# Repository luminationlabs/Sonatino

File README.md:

# Sonatino "Bluetooth Audio Edition" PCB Design Files

This is an unreleased variant of the [Sonatino](https://github.com/luminationlabs/Sonatino) board that adds support for Bluetooth audio by using the ESP32 microcontroller in place of ESP32-S3.

## Features

- ESP32-WROOM-32UE MCU with 16MB flash
- High-quality 24-bit/192kHz DAC (WM8524, stereo) and ADC (WM8782, mono)
- 3.2W speaker amplifier (MAX98357A)
- TRRS audio jack supporting input and output
- Stereo headphone amplifier and microphone preamp
- microSD card slot
- WiFi and Bluetooth v4.2 BR/EDR and BLE
- Bluetooth audio (A2DP) support
- USB-C for programming and power
- Battery support with charging circuit
- Configurable audio I/O levels
- Compact form factor

## Component Availability

The ADC that Sonatino uses (Cirrus Logic WM8782) has been discontinued by its manufacturer. Some suppliers may still have limited stock, but ultimately it needs to be replaced with a similar ADC (possibly a Texas Instruments PCM186x chip or an audio CODEC to replace the ADC and DAC). In either case, the PCB schematic and layout will need to be modified as there is no drop-in replacement.

## Board Variants

### [Sonatino](https://github.com/luminationlabs/Sonatino) (`main` branch)

- Standard board documented at [sonatino.com](https://sonatino.com)
- Based on ESP32-S3-WROOM-1U
- Uses Bluetooth 5.0 LE **without** support for Bluetooth audio

### [Sonatino - Bluetooth Audio Edition](https://github.com/luminationlabs/Sonatino/tree/btaudio) (`btaudio` branch)

- Unreleased board
- Based on ESP32-WROOM-32UE
- Uses Bluetooth v4.2 BR/EDR **with** support for Bluetooth audio (A2DP)
- Has fewer exposed GPIO pins (10 vs 13)
- Requires configuration using shift register on GPIO 17, 18, and 19

## License and Trademark Notice

Certified open source hardware ([oshwa.org/cert](https://oshwa.org/cert)) - [OSHW] US002724

The design files for this PCB are open-source hardware under [CERN OHL-P v2.0](https://ohwr.org/cern_ohl_p_v2.txt).

The name "Sonatino" and the associated logo are trademarks of Lumination Labs, Inc. Other manufacturers may use the hardware design but may not use the "Sonatino" branding without permission.

The documentation for Sonatino is copyrighted by Lumination Labs, Inc. and provided for informational purposes only. Redistribution or modification of the documentation requires written permission.

## Documentation

Documentation and examples for the standard Sonatino board (not this variant) can be found here:

- [Documentation](https://sonatino.com/docs/)
- [Example Projects](https://github.com/luminationlabs/Sonatino-Examples)

Pin configurations will need to be modified for use with the "Bluetooth Audio Edition" according to those found in the schematic. Audio configuration requires the use of a shift register on GPIO 17, 18, and 19 (SER, SRCLK, and RCLK).

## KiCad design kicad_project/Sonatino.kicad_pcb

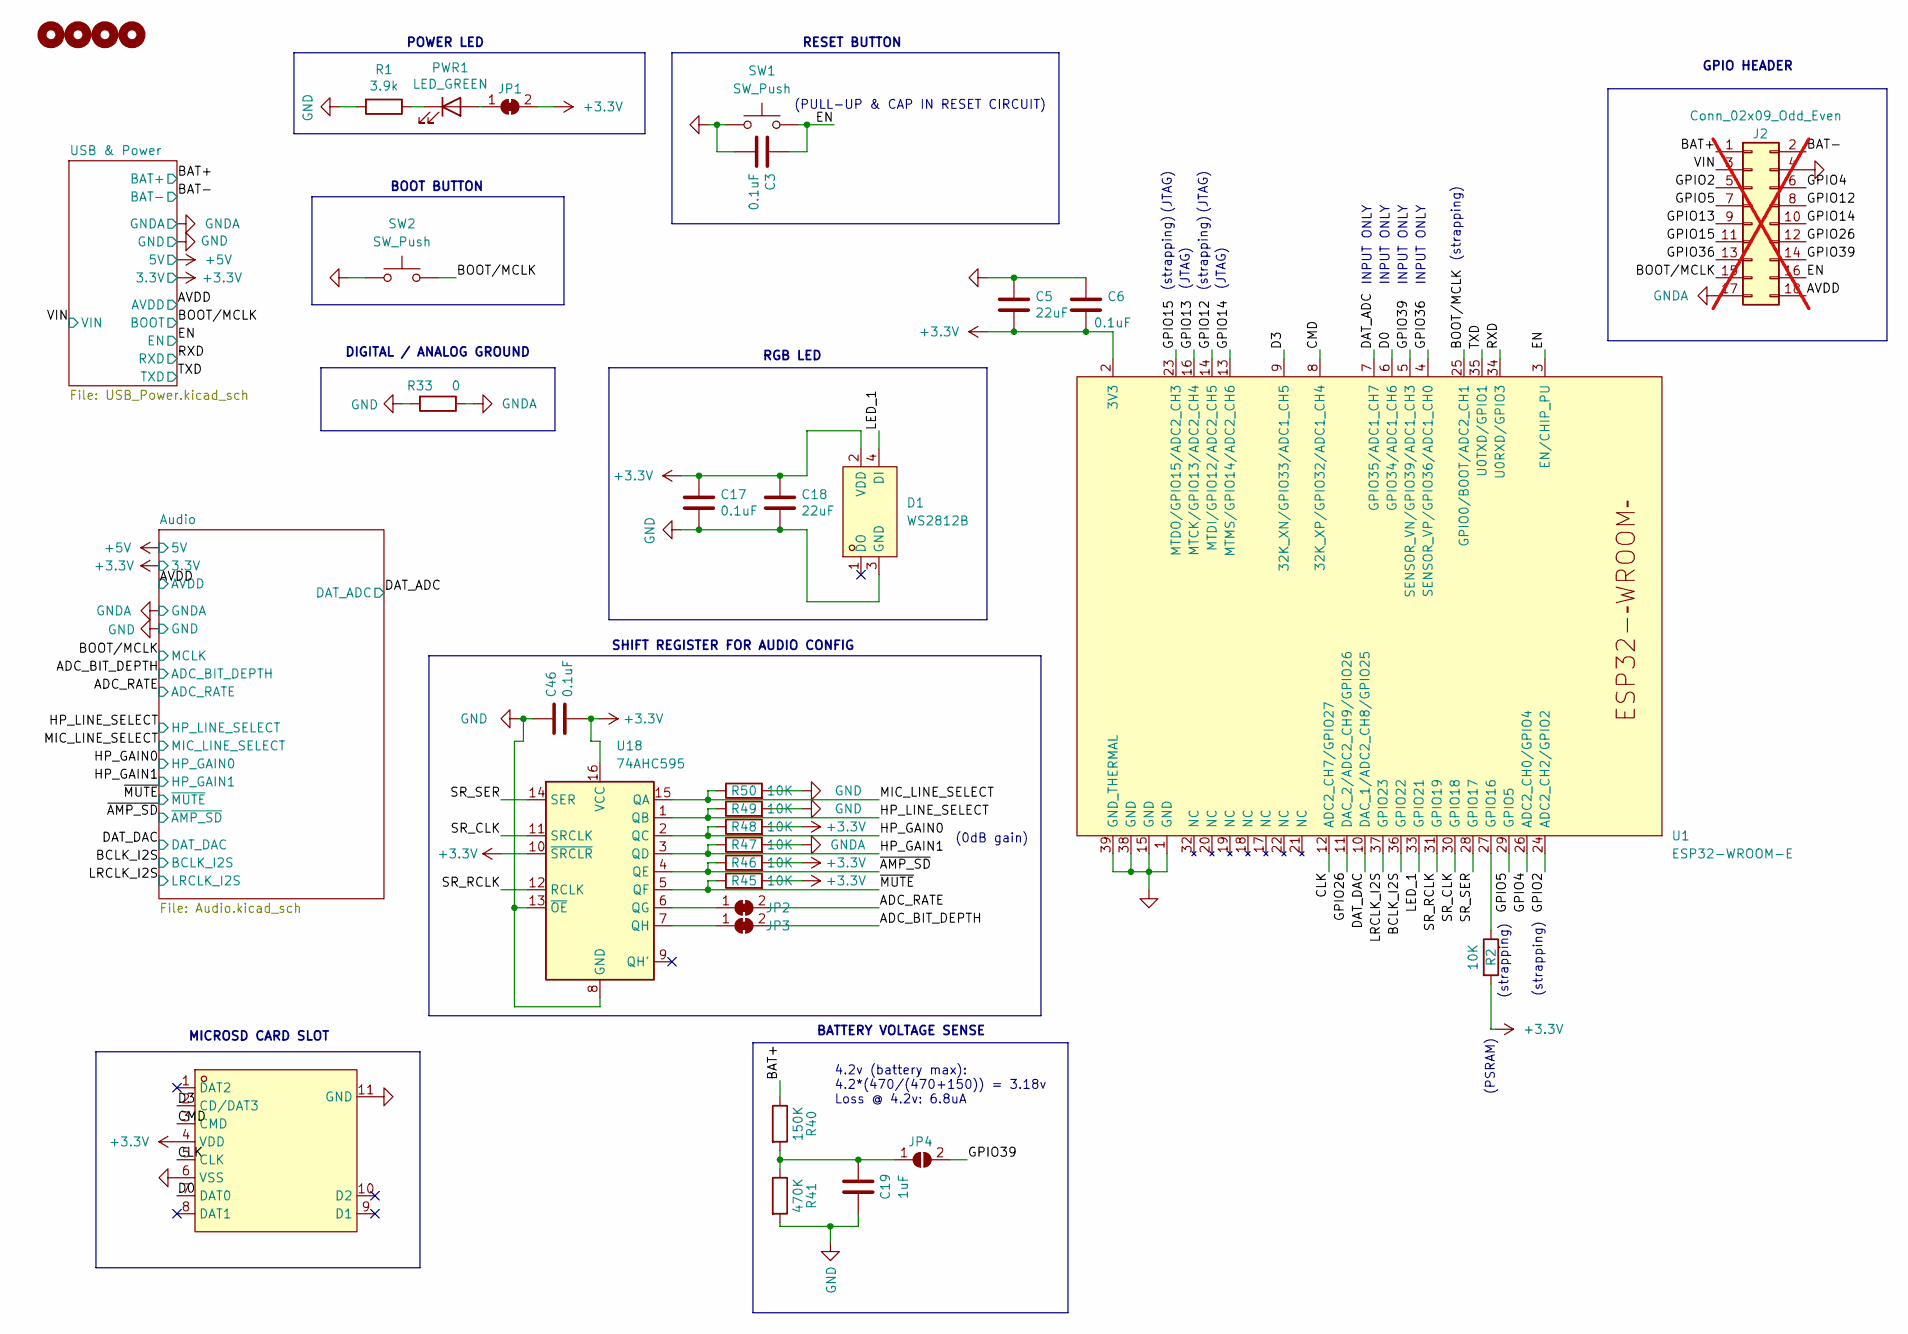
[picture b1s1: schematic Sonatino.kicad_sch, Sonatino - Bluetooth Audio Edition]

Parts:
C3, C6, C17, C46: 0.1uF; C_0402_1005Metric; LCSC C307331
C5: 22uF; C_0805_2012Metric; LCSC C45783
C18: 22uF; C_0603_1608Metric; LCSC C59461
C19: 1uF; C_0402_1005Metric; LCSC C52923
Card1: TF-008; TF-SMD_TF-008; LCSC Part C428465
D1: WS2812B; LED-SMD_4P-L1.6-W1.5_XL-1615RGBC-WS2812B; LCSC C5349954
H1, H3, H5, H7: MountingHole; MountingHole_2.7mm_Pad; LCSC 0
J2: Conn_02x09_Odd_Even; PinHeader_2x09_P2.54mm_Vertical; LCSC 0; not fitted
JP1, JP2, JP3: SolderJumper_2_Bridged; SolderJumper-2_P1.3mm_Bridged_Pad1.0x1.5mm; LCSC 0
JP4: SolderJumper_2_Open; SolderJumper-2_P1.3mm_Open_TrianglePad1.0x1.5mm
PWR1: LED_GREEN; LED_0603_1608Metric; LCSC C12624
R1: 3.9k; R_0402_1005Metric; LCSC C51721
R2, R45, R46, R47, R48, R49, R50: 10K; R_0402_1005Metric; LCSC C25744
R33: 0; R_0603_1608Metric; LCSC C21189
R40: 150K; R_0402_1005Metric; LCSC C102813
R41: 470K; R_0402_1005Metric; LCSC C25790
SW1, SW2: SW_Push; SW_Push_1P1T_NO_3.95_2.9; LCSC C354946
U1: ESP32-WROOM-E; ESP32-WROOM-32UE; LCSC C701346
U18: 74AHC595; X1-QFN-16-EP_L2.5-W2.5-P0.40-BL-EP1.4; LCSC C2682068

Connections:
+3.3V: C5.2, C6.2, C17.1, C18.1, C46.2, Card1.4 (VDD), D1.2 (VDD), JP1.2 (B), R2.2, R45.2, R46.2, R48.2, U1.2 (3V3), U18.10 (~SRCLR), U18.16 (VCC); also elsewhere on the board
/ADC_BIT_DEPTH: JP3.2 (B); also elsewhere on the board
/ADC_RATE: JP2.2 (B); also elsewhere on the board
/AVDD: J2.18; also elsewhere on the board
/BAT+: J2.1, R40.1; also elsewhere on the board
/BAT-: J2.2; also elsewhere on the board
/BCLK_I2S: U1.36 (GPIO22); also elsewhere on the board
/BOOT/MCLK: J2.15, SW2.2, U1.25 (GPIO0/BOOT/ADC2_CH1); also elsewhere on the board
/CLK: Card1.5 (CLK), U1.12 (ADC2_CH7/GPIO27)
/CMD: Card1.3 (CMD), U1.8 (32K_XP/GPIO32/ADC1_CH4)
/D0: Card1.7 (DAT0), U1.6 (GPIO34/ADC1_CH6)
/D3: Card1.2 (CD/DAT3), U1.9 (32K_XN/GPIO33/ADC1_CH5)
/DAT_ADC: U1.7 (GPIO35/ADC1_CH7); also elsewhere on the board
/DAT_DAC: U1.10 (DAC_1/ADC2_CH8/GPIO25); also elsewhere on the board
/EN: C3.1, J2.16, SW1.2, U1.3 (EN/CHIP_PU); also elsewhere on the board
/GPIO2: J2.5, U1.24 (ADC2_CH2/GPIO2)
/GPIO4: J2.6, U1.26 (ADC2_CH0/GPIO4)
/GPIO5: J2.7, U1.29 (GPIO5)
/GPIO12: J2.8, U1.14 (MTDI/GPIO12/ADC2_CH5)
/GPIO13: J2.9, U1.16 (MTCK/GPIO13/ADC2_CH4)
/GPIO14: J2.10, U1.13 (MTMS/GPIO14/ADC2_CH6)
/GPIO15: J2.11, U1.23 (MTDO/GPIO15/ADC2_CH3)
/GPIO26: J2.12, U1.11 (DAC_2/ADC2_CH9/GPIO26)
/GPIO36: J2.13, U1.4 (SENSOR_VP/GPIO36/ADC1_CH0)
/GPIO39: J2.14, JP4.2 (B), U1.5 (SENSOR_VN/GPIO39/ADC1_CH3)
/HP_GAIN0: R48.1, U18.2 (QC); also elsewhere on the board
/HP_GAIN1: R47.1, U18.3 (QD); also elsewhere on the board
/HP_LINE_SELECT: R49.1, U18.1 (QB); also elsewhere on the board
/LED_1: D1.4 (DI), U1.33 (GPIO21)
/LRCLK_I2S: U1.37 (GPIO23); also elsewhere on the board
/MIC_LINE_SELECT: R50.1, U18.15 (QA); also elsewhere on the board
/RXD: U1.34 (U0RXD/GPIO3); also elsewhere on the board
/SR_CLK: U1.30 (GPIO18), U18.11 (SRCLK)
/SR_RCLK: U1.31 (GPIO19), U18.12 (RCLK)
/SR_SER: U1.28 (GPIO17), U18.14 (SER)
/TXD: U1.35 (U0TXD/GPIO1); also elsewhere on the board
/VIN: J2.3; also elsewhere on the board
/~AMP_SD: R46.1, U18.4 (QE); also elsewhere on the board
/~MUTE: R45.1, U18.5 (QF); also elsewhere on the board
GND: C3.2, C5.1, C6.1, C17.2, C18.2, C19.1, C46.1, Card1.6 (VSS), Card1.11 (GND), D1.3 (GND), J2.4, R1.2, R33.2, R41.2, R49.2, R50.2, SW1.1, SW2.1, U1.1 (GND), U1.15 (GND), U1.38 (GND), U1.39 (GND_THERMAL), U18.8 (GND), U18.13 (~OE); also elsewhere on the board
GNDA: J2.17, R33.1, R47.2; also elsewhere on the board
unnamed: JP1.1 (A), PWR1.2 (A)
unnamed: JP2.1 (A), U18.6 (QG)
unnamed: JP3.1 (A), U18.7 (QH)
unnamed: C19.2, JP4.1 (A), R40.2, R41.1
unnamed: PWR1.1 (K), R1.1
unnamed: R2.1, U1.27 (GPIO16)

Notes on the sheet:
(PSRAM)
(JTAG)
GPIO HEADER
(strapping)
POWER LED
MICROSD CARD SLOT
INPUT ONLY
RESET BUTTON
BOOT BUTTON
BATTERY VOLTAGE SENSE
(0dB gain)
(PULL-UP & CAP IN RESET CIRCUIT)
DIGITAL / ANALOG GROUND
RGB LED
4.2v (battery max): 4.2*(470/(470+150)) = 3.18v Loss @ 4.2v: 6.8uA
SHIFT REGISTER FOR AUDIO CONFIG

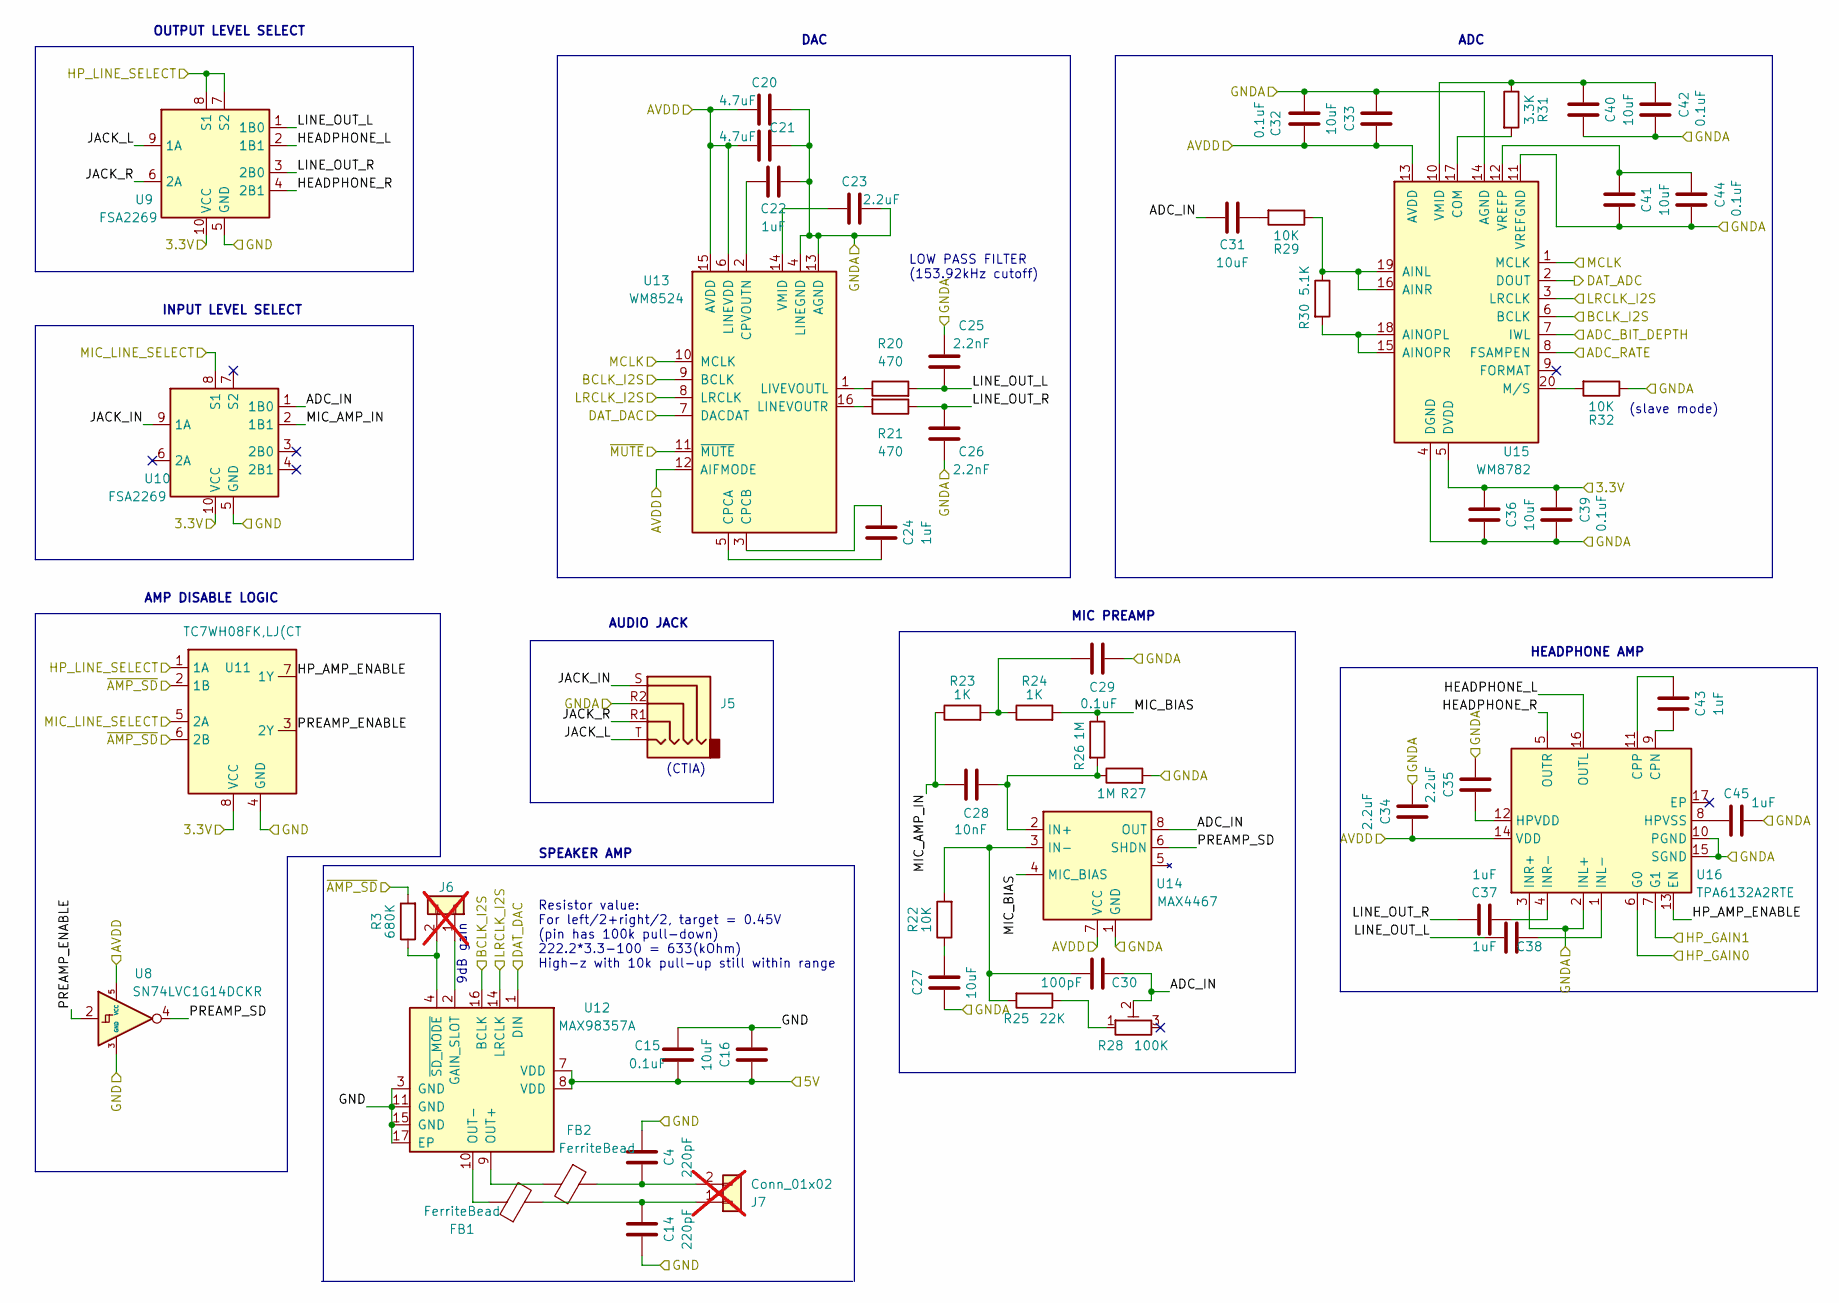
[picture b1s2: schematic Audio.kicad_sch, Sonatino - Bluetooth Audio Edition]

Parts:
C4, C14: 220pF; C_0402_1005Metric; LCSC C1530
C15: 0.1uF; C_0805_2012Metric; LCSC C49678
C16: 10uF; C_0805_2012Metric; LCSC C15850
C20, C21: 4.7uF; C_0402_1005Metric; LCSC C23733
C22, C37, C38, C43, C45: 1uF; C_0402_1005Metric; LCSC C52923
C23, C34, C35: 2.2uF; C_0402_1005Metric; LCSC C12530
C24: 1uF; C_0603_1608Metric; LCSC C15849
C25, C26: 2.2nF; C_0402_1005Metric; LCSC C1531
C27, C31, C33, C36, C40, C41: 10uF; C_0402_1005Metric; LCSC C15525
C28: 10nF; C_0402_1005Metric; LCSC C15195
C29, C32, C39, C42, C44: 0.1uF; C_0402_1005Metric; LCSC C307331
C30: 100pF; C_0402_1005Metric; LCSC C1546
FB1, FB2: FerriteBead; L_0603_1608Metric; LCSC C1002
J5: AudioJack4; PJ-321B; LCSC C692436
J6: Conn_01x02; PinHeader_1x02_P2.54mm_Vertical; not fitted
J7: Conn_01x02; PinHeader_1x02_P2.54mm_Vertical; LCSC 0; not fitted
R3: 680K; R_0603_1608Metric; LCSC C25822
R20, R21: 470; R_0402_1005Metric; LCSC C25117
R22, R29, R32: 10K; R_0402_1005Metric; LCSC C25744
R23, R24: 1K; R_0402_1005Metric; LCSC C11702
R25: 22K; R_0402_1005Metric; LCSC C25768
R26, R27: 1M; R_0402_1005Metric; LCSC C26083
R28: 100K; G32AT-B103; LCSC C128123
R30: 5.1K; R_0402_1005Metric; LCSC C25905
R31: 3.3K; R_0402_1005Metric; LCSC C25890
U8: SN74LVC1G14DCKR; SOT-353_SC-70-5; LCSC C2976657
U9, U10: FSA2269; Fairchild_MicroPak-10_2.10x1.6mm_P0.5mm; LCSC C895405
U11: TC7WH08FK,LJ(CT; VSSOP-8_2.3x2mm_P0.5mm; LCSC C2880449
U12: MAX98357A; TQFN-16-1EP_3x3mm_P0.5mm_EP1.23x1.23mm; JLCPCB Rotation Offset 270
U13: WM8524; TSSOP-16_4.4x5mm_P0.65mm; LCSC C146242
U14: MAX4467; SOT-23-8; LCSC C490742
U15: WM8782; SSOP-20_5.3x7.2mm_P0.65mm; LCSC C323842
U16: TPA6132A2RTE; WQFN-16-1EP_3x3mm_P0.5mm_EP1.6x1.6mm_ThermalVias; LCSC C69901

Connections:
+3.3V: C36.2, C39.1, U9.10 (VCC), U10.10 (VCC), U11.8 (VCC), U15.5 (DVDD); also elsewhere on the board
+5V: C15.1, C16.2, U12.7 (VDD), U12.8 (VDD); also elsewhere on the board
/ADC_BIT_DEPTH: U15.7 (IWL); also elsewhere on the board
/ADC_RATE: U15.8 (FSAMPEN); also elsewhere on the board
/AVDD: C20.1, C21.1, C32.1, C33.2, C34.2, U8.5 (VCC), U13.6 (LINEVDD), U13.12 (AIFMODE), U13.15 (AVDD), U14.7 (VCC), U15.13 (AVDD), U16.14 (VDD); also elsewhere on the board
/Audio/ADC_IN: C30.2, C31.1, R28.2, U10.1 (1B0), U14.8 (OUT)
/Audio/HEADPHONE_L: U9.2 (1B1), U16.16 (OUTL)
/Audio/HEADPHONE_R: U9.4 (2B1), U16.5 (OUTR)
/Audio/HP_AMP_ENABLE: U11.7 (1Y), U16.13 (EN)
/Audio/JACK_IN: J5.S, U10.9 (1A)
/Audio/JACK_L: J5.T, U9.9 (1A)
/Audio/JACK_R: J5.R1, U9.6 (2A)
/Audio/LINE_OUT_L: C25.1, C38.1, R20.2, U9.1 (1B0)
/Audio/LINE_OUT_R: C26.2, C37.2, R21.1, U9.3 (2B0)
/Audio/MIC_AMP_IN: C28.2, R23.1, U10.2 (1B1)
/Audio/MIC_BIAS: R24.2, R26.1, U14.4 (MIC_BIAS)
/Audio/PREAMP_ENABLE: U8.2, U11.3 (2Y)
/Audio/PREAMP_SD: U8.4, U14.6 (SHDN)
/BCLK_I2S: U12.16 (BCLK), U13.9 (BCLK), U15.6 (BCLK); also elsewhere on the board
/BOOT/MCLK: U13.10 (MCLK), U15.1 (MCLK); also elsewhere on the board
/DAT_ADC: U15.2 (DOUT); also elsewhere on the board
/DAT_DAC: U12.1 (DIN), U13.7 (DACDAT); also elsewhere on the board
/HP_GAIN0: U16.6 (G0); also elsewhere on the board
/HP_GAIN1: U16.7 (G1); also elsewhere on the board
/HP_LINE_SELECT: U9.7 (S2), U9.8 (S1), U11.1 (1A); also elsewhere on the board
/LRCLK_I2S: U12.14 (LRCLK), U13.8 (LRCLK), U15.3 (LRCLK); also elsewhere on the board
/MIC_LINE_SELECT: U10.8 (S1), U11.5 (2A); also elsewhere on the board
/~AMP_SD: R3.2, U11.2 (1B), U11.6 (2B); also elsewhere on the board
/~MUTE: U13.11 (~MUTE); also elsewhere on the board
GND: C4.2, C14.1, C15.2, C16.1, U8.3 (GND), U9.5 (GND), U10.5 (GND), U11.4 (GND), U12.3 (GND), U12.11 (GND), U12.15 (GND), U12.17 (EP); also elsewhere on the board
GNDA: C20.2, C21.2, C22.2, C23.1, C25.2, C26.1, C27.2, C29.1, C32.2, C33.1, C34.1, C35.1, C36.1, C39.2, C40.1, C41.1, C42.2, C44.2, C45.1, J5.R2, R27.2, R32.1, U13.4 (LINEGND), U13.13 (AGND), U14.1 (GND), U15.4 (DGND), U15.11 (VREFGND), U15.14 (AGND), U16.2 (INL+), U16.3 (INR+), U16.10 (PGND), U16.15 (SGND); also elsewhere on the board
unnamed: C27.1, R22.1
unnamed: C29.2, R23.2, R24.1
unnamed: C31.2, R29.2
unnamed: J6.1, U12.2 (GAIN_SLOT)
unnamed: J6.2, R3.1, U12.4 (~SD_MODE)
unnamed: C14.2, FB1.2, J7.1
unnamed: C4.1, FB2.1, J7.2
unnamed: R25.1, R28.1
unnamed: FB2.2, U12.9 (OUT+)
unnamed: FB1.1, U12.10 (OUT-)
unnamed: C24.1, U13.5 (CPCA)
unnamed: C24.2, U13.3 (CPCB)
unnamed: C22.1, U13.2 (CPVOUTN)
unnamed: R21.2, U13.16 (LINEVOUTR)
unnamed: R20.1, U13.1 (LIVEVOUTL)
unnamed: C23.2, U13.14 (VMID)
unnamed: C28.1, R26.2, R27.1, U14.2 (IN+)
unnamed: C30.1, R22.2, R25.2, U14.3 (IN-)
unnamed: R29.1, R30.1, U15.16 (AINR), U15.19 (AINL)
unnamed: R30.2, U15.15 (AINOPR), U15.18 (AINOPL)
unnamed: R31.2, U15.17 (COM)
unnamed: R32.2, U15.20 (M/S)
unnamed: C40.2, C42.1, R31.1, U15.10 (VMID)
unnamed: C41.2, C44.1, U15.12 (VREFP)
unnamed: C43.1, U16.9 (CPN)
unnamed: C43.2, U16.11 (CPP)
unnamed: C35.2, U16.12 (HPVDD)
unnamed: C45.2, U16.8 (HPVSS)
unnamed: C38.2, U16.1 (INL-)
unnamed: C37.1, U16.4 (INR-)

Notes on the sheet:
ADC
MIC PREAMP
LOW PASS FILTER (153.92kHz cutoff)
Resistor value: For left/2+right/2, target = 0.45V (pin has 100k pull-down) 222.2*3.3-100 = 633(kOhm) High-z with 10k pull-up still within range
INPUT LEVEL SELECT
(slave mode)
AMP DISABLE LOGIC
AUDIO JACK
OUTPUT LEVEL SELECT
DAC
SPEAKER AMP
HEADPHONE AMP
(CTIA)
9dB gain

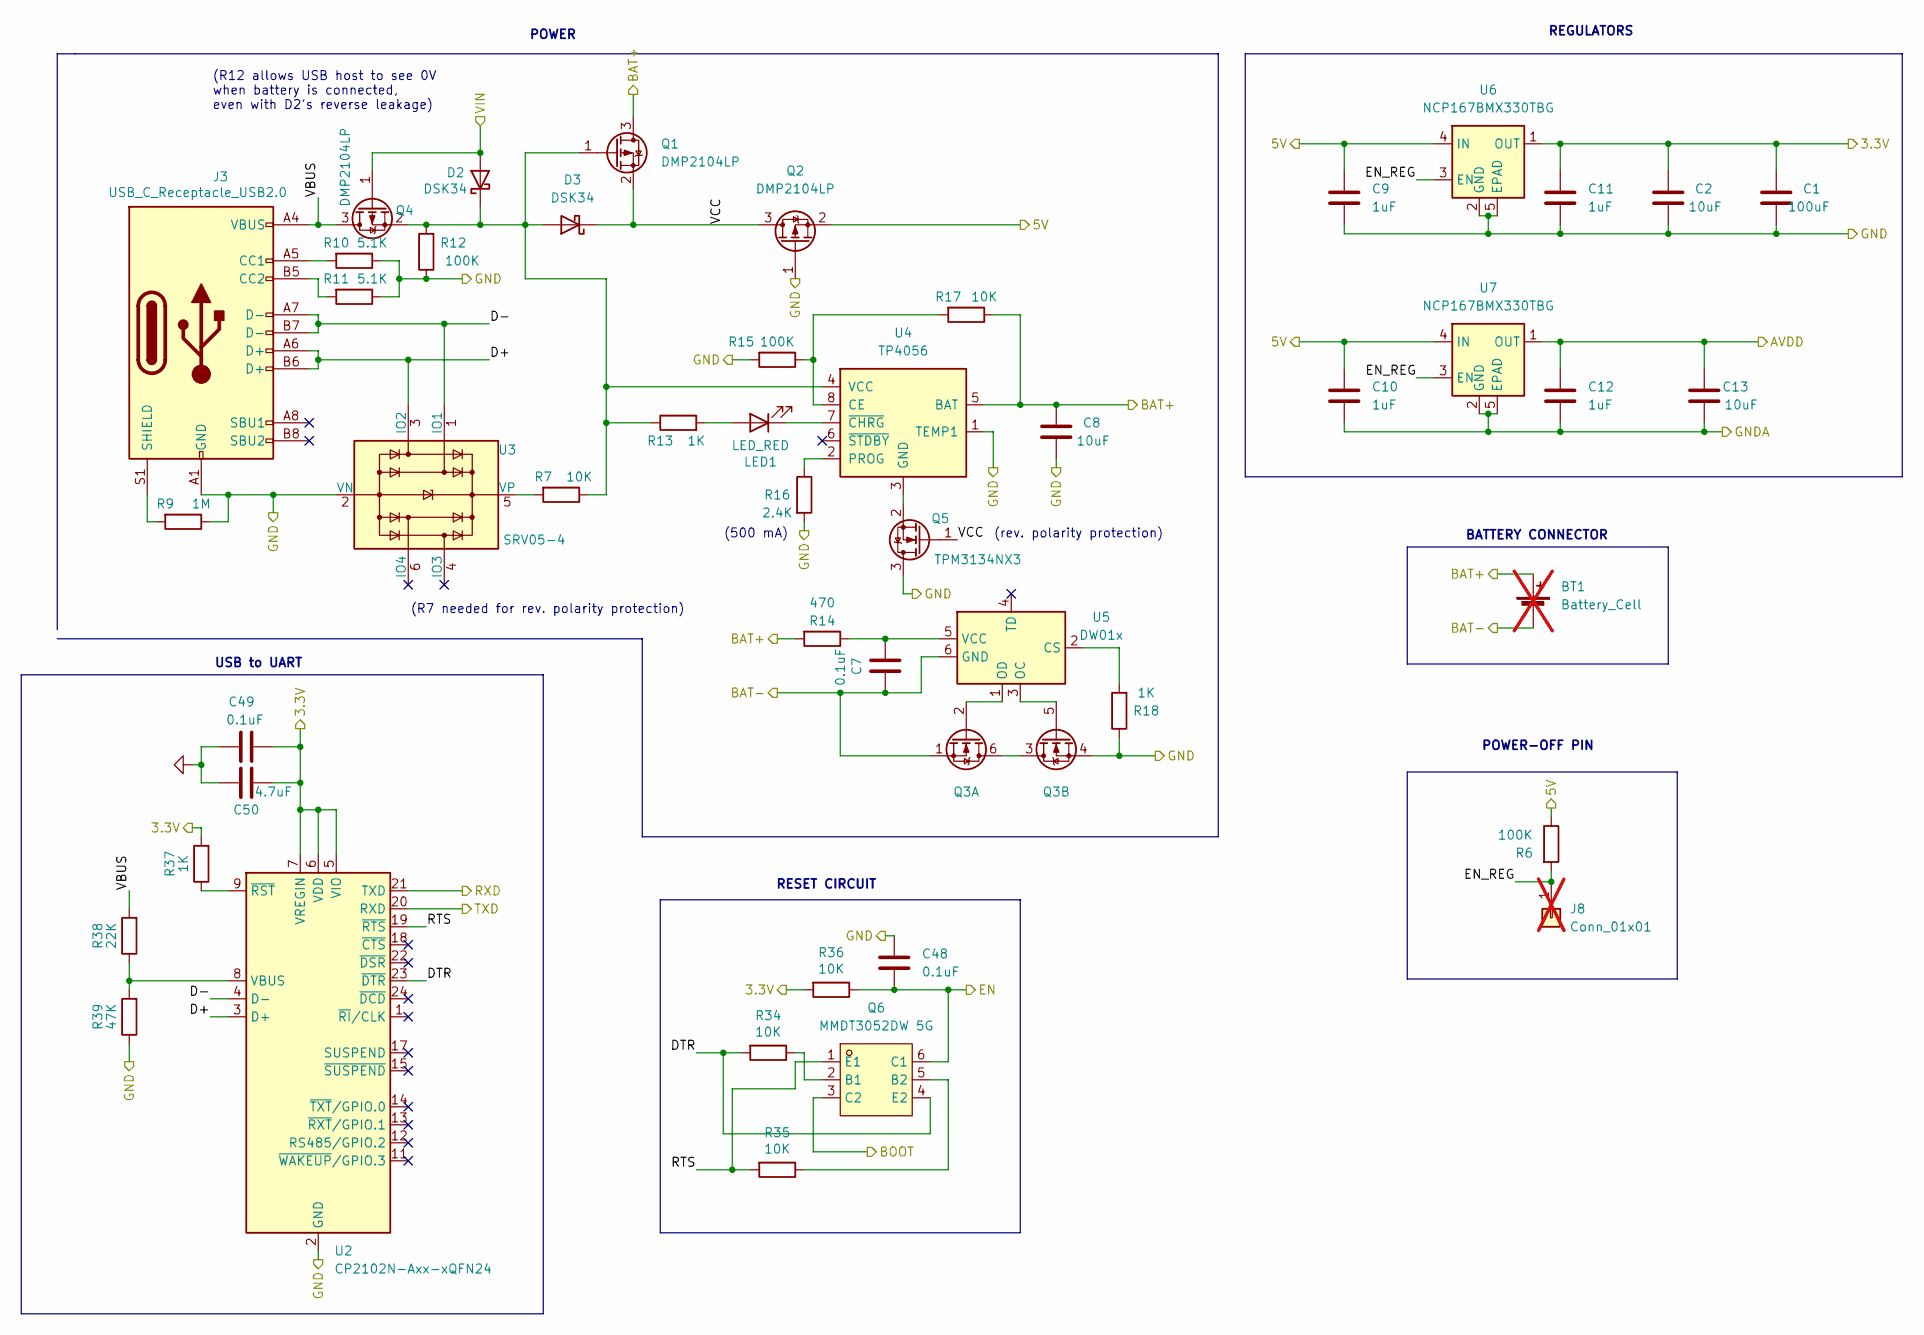
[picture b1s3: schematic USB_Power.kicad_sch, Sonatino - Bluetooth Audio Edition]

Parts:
BT1: Battery_Cell; JST_PH_S2B-PH-SM4-TB_1x02-1MP_P2.00mm_Horizontal; LCSC 0; not fitted
C1: 100uF; C_1206_3216Metric; LCSC C15008
C2, C13: 10uF; C_0603_1608Metric; LCSC C19702
C7, C48, C49: 0.1uF; C_0402_1005Metric; LCSC C307331
C8: 10uF; C_0402_1005Metric; LCSC C15525
C9, C10, C11, C12: 1uF; C_0402_1005Metric; LCSC C52923
C50: 4.7uF; C_0402_1005Metric; LCSC C23733
D2, D3: DSK34; SOD-123FL; LCSC C41029
J3: USB_C_Receptacle_USB2.0; USB_C_Receptacle_HRO_TYPE-C-31-M-12; LCSC C165948
J8: Conn_01x01; PinHeader_1x01_P2.54mm_Vertical; LCSC 0; not fitted
LED1: LED_RED; LED_0603_1608Metric; LCSC C2286
Q1, Q2, Q4: DMP2104LP; Diodes_DFN1411-3; LCSC C260933
Q3: HSCC8233; DFN-6-1EP_3x2mm_P0.5mm_EP1.65x1.35mm_Dual_MOSFETs; LCSC C700968
Q5: TPM3134NX3; SOT-723; LCSC C558450
Q6: MMDT3052DW 5G; SOT-363_SC-70-6; LCSC C2928254
R6, R12, R15: 100K; R_0402_1005Metric; LCSC C25741
R7, R17, R34, R35, R36: 10K; R_0402_1005Metric; LCSC C25744
R9: 1M; R_0402_1005Metric; LCSC C26083
R10, R11: 5.1K; R_0402_1005Metric; LCSC C25905
R13, R18, R37: 1K; R_0402_1005Metric; LCSC C11702
R14: 470; R_0402_1005Metric; LCSC C25117
R16: 2.4K; R_0402_1005Metric; LCSC C25882
R38: 22K; R_0402_1005Metric; LCSC C25768
R39: 47K; R_0402_1005Metric; LCSC C25792
U2: CP2102N-Axx-xQFN24; QFN-24-1EP_4x4mm_P0.5mm_EP2.6x2.6mm; LCSC C969151
U3: SRV05-4; SOT-23-6; LCSC C85364
U4: TP4056; TI_SO-PowerPAD-8; LCSC C16581
U5: DW01x; SOT-23-6; LCSC C351410
U6, U7: NCP167BMX330TBG; OnSemi_XDFN4-1EP_1.0x1.0mm_EP0.52x0.52mm-FIXED; LCSC C892227

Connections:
+3.3V: C1.2, C2.2, C11.1, C49.2, C50.1, R36.2, R37.2, U2.5 (VIO), U2.6 (VDD), U2.7 (VREGIN), U6.1 (OUT); also elsewhere on the board
+5V: C9.1, C10.1, Q2.2 (S), R6.1, U6.4 (IN), U7.4 (IN); also elsewhere on the board
/AVDD: C12.1, C13.2, U7.1 (OUT); also elsewhere on the board
/BAT+: BT1.1 (+), C8.2, Q1.3 (D), R14.2, R17.1, U4.5 (BAT); also elsewhere on the board
/BAT-: BT1.2 (-), C7.1, Q3.1 (S), U5.6 (GND); also elsewhere on the board
/BOOT/MCLK: Q6.3 (C2); also elsewhere on the board
/EN: C48.2, Q6.6 (C1), R36.1; also elsewhere on the board
/RXD: U2.21 (TXD); also elsewhere on the board
/TXD: U2.20 (RXD); also elsewhere on the board
/USB & Power/D+: J3.A6 (D+), J3.B6 (D+), U2.3 (D+), U3.3 (IO2)
/USB & Power/D-: J3.A7 (D-), J3.B7 (D-), U2.4 (D-), U3.1 (IO1)
/USB & Power/DTR: Q6.4 (E2), R34.2, U2.23 (~DTR)
/USB & Power/EN_REG: J8.1, R6.2, U6.3 (EN), U7.3 (EN)
/USB & Power/RTS: Q6.1 (E1), R35.2, U2.19 (~RTS)
/USB & Power/VBUS: J3.A4 (VBUS), J3.A9 (VBUS), J3.B4 (VBUS), J3.B9 (VBUS), Q4.3 (D), R38.2
/USB & Power/VCC: D3.1 (K), Q1.2 (S), Q2.3 (D), Q5.1 (G)
/VIN: D2.2 (A), Q4.1 (G); also elsewhere on the board
GND: C1.1, C2.1, C8.1, C9.2, C11.2, C48.1, C49.1, C50.2, J3.A1 (GND), J3.A12 (GND), J3.B1 (GND), J3.B12 (GND), Q2.1 (G), Q3.4 (S), Q5.3 (D), R9.1, R10.1, R11.1, R12.1, R15.2, R16.2, R18.1, R39.1, U2.2 (GND), U2.25 (GND), U3.2 (VN), U4.1 (TEMP1), U6.2 (GND), U6.5 (EPAD); also elsewhere on the board
GNDA: C10.2, C12.2, C13.1, U7.2 (GND), U7.5 (EPAD); also elsewhere on the board
unnamed: D2.1 (K), D3.2 (A), Q1.1 (G), Q4.2 (S), R7.1, R12.2, R13.1, U4.4 (VCC)
unnamed: J3.A5 (CC1), R10.2
unnamed: J3.B5 (CC2), R11.2
unnamed: J3.S1 (SHIELD), R9.2
unnamed: LED1.2 (A), R13.2
unnamed: LED1.1 (K), U4.7 (~CHRG)
unnamed: Q3.3 (D), Q3.6 (D)
unnamed: Q3.2 (G), U5.1 (OD)
unnamed: Q3.5 (G), U5.3 (OC)
unnamed: Q5.2 (S), U4.3 (GND)
unnamed: Q6.2 (B1), R34.1
unnamed: Q6.5 (B2), R35.1
unnamed: R38.1, R39.2, U2.8 (VBUS)
unnamed: R37.1, U2.9 (~RST)
unnamed: R7.2, U3.5 (VP)
unnamed: R15.1, R17.2, U4.8 (CE)
unnamed: R16.1, U4.2 (PROG)
unnamed: R18.2, U5.2 (CS)
unnamed: C7.2, R14.1, U5.5 (VCC)

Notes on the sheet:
(rev. polarity protection)
RESET CIRCUIT
POWER-OFF PIN
(500 mA)
USB to UART
POWER
REGULATORS
(R7 needed for rev. polarity protection)
BATTERY CONNECTOR
(R12 allows USB host to see 0V when battery is connected, even with D2's reverse leakage)

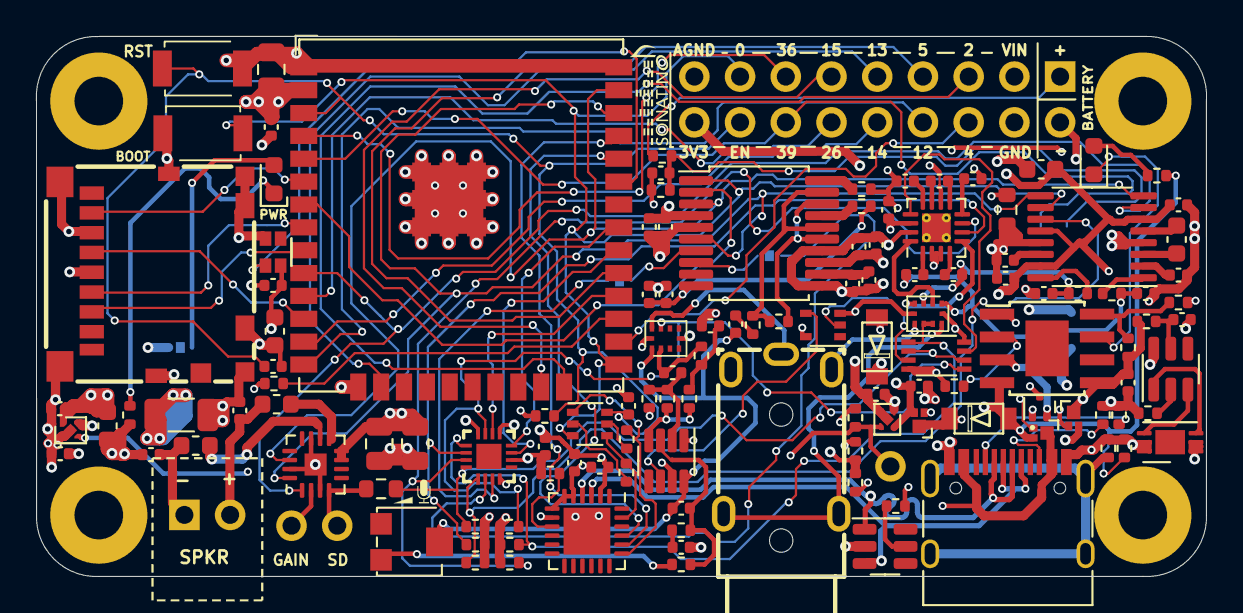
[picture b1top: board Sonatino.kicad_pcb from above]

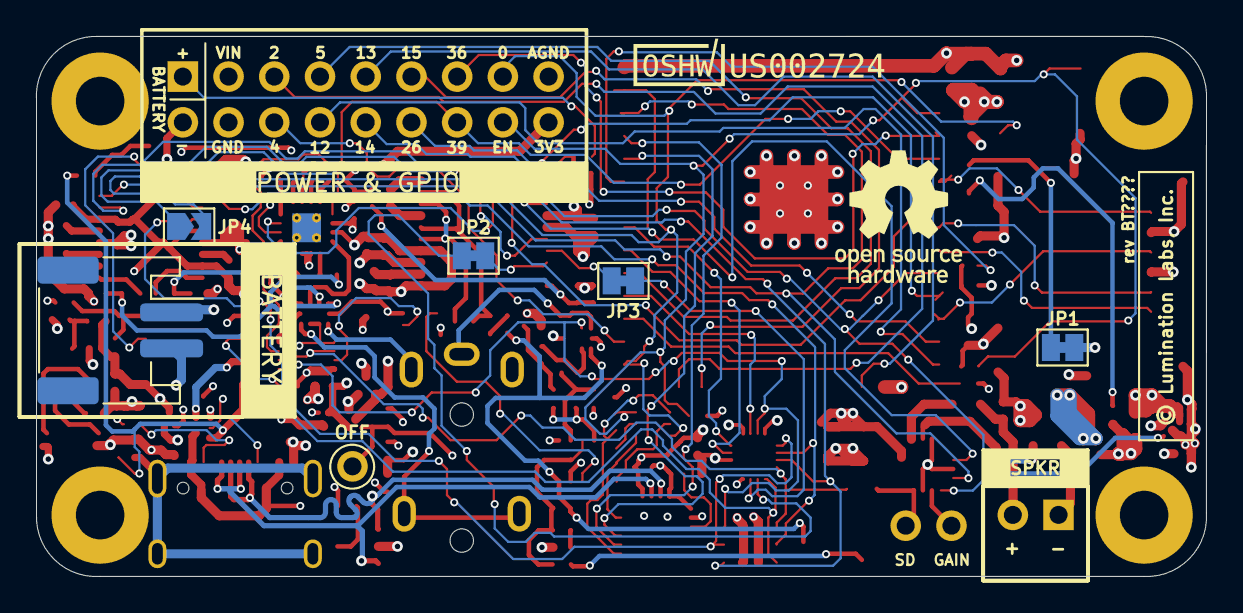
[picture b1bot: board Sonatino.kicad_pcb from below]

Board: 4 copper layers, 65.0 x 30.0 mm, 140 parts (5 on the bottom side), 117 nets.

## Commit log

2025-02-25 Add OSHWA certification mark and info

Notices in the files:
kicad_project/Sonatino.kicad_pcb:
© Lumination Labs, Inc.
